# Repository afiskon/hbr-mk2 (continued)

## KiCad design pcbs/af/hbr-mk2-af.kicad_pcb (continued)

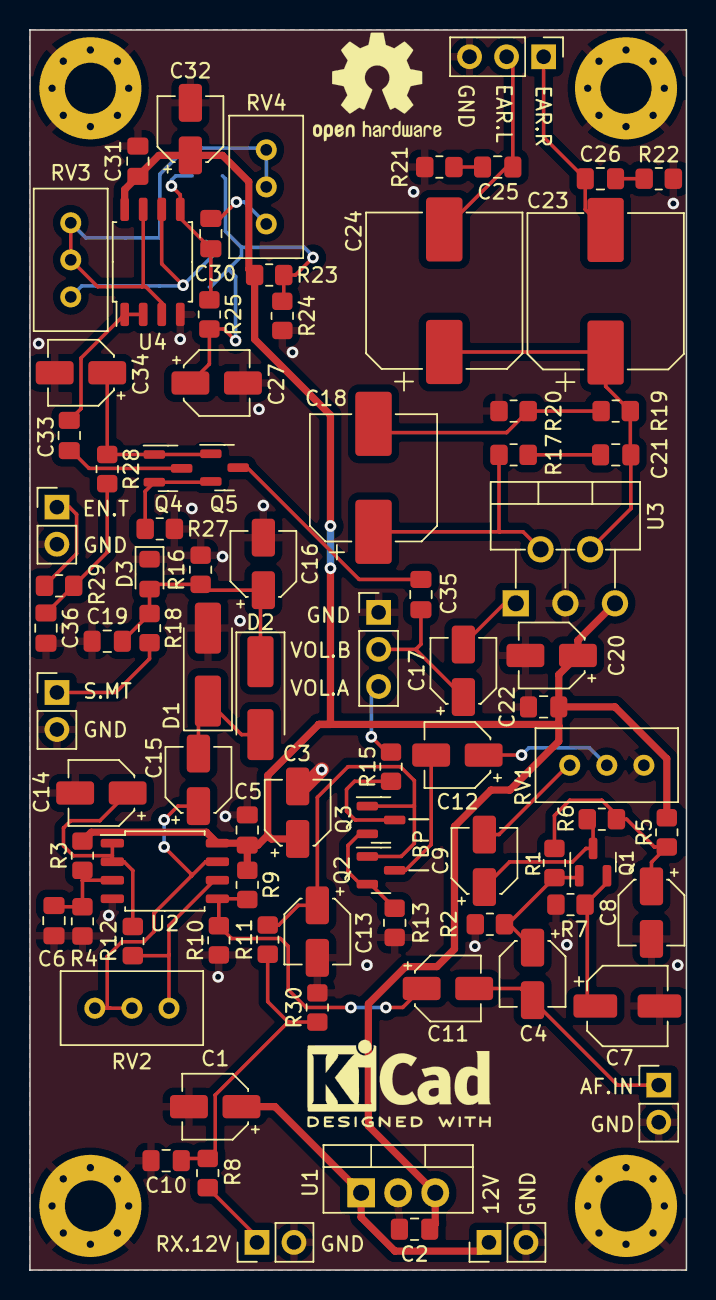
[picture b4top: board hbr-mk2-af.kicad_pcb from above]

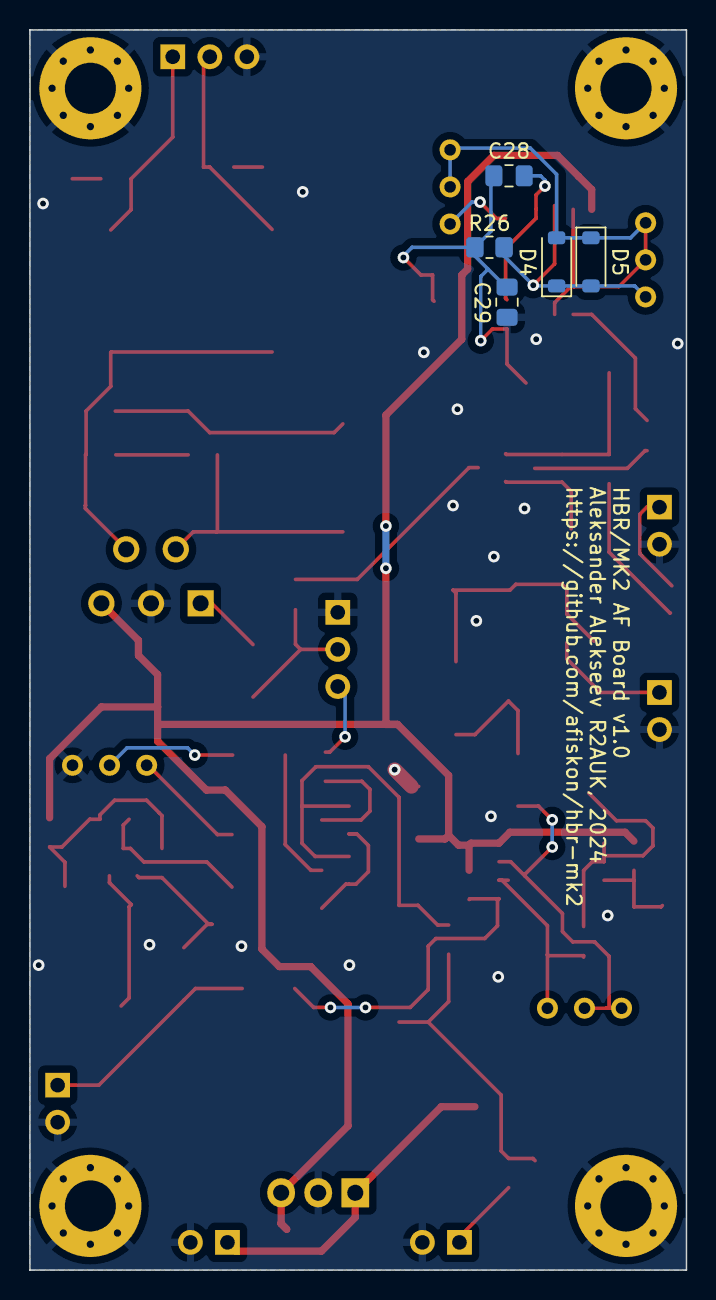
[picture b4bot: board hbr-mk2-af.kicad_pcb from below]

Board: 2 copper layers, 45.0 x 85.0 mm, 96 parts (5 on the bottom side), 47 nets.

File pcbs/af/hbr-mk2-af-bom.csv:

Reference(s),Qty,Value,Footprint
C1,1,1u,Capacitor_SMD:CP_Elec_4x5.4
"C2, C5, C6, C10, C19, C21, C22, C25, C26, C29, C31, C33, C36",13,0.1u,Capacitor_SMD:C_0805_2012Metric_Pad1.18x1.45mm_HandSolder
"C3, C4, C8, C9, C11, C12, C14, C15, C16, C20, C27, C32",12,10u,Capacitor_SMD:CP_Elec_4x5.4
C7,1,22u,Capacitor_SMD:CP_Elec_5x5.4
"C13, C34",2,4.7u,Capacitor_SMD:CP_Elec_4x5.4
C17,1,1u,Capacitor_SMD:CP_Elec_4x5.4
C18,1,220u,Capacitor_SMD:CP_Elec_8x10.5
"C23, C24",2,470u,Capacitor_SMD:CP_Elec_10x10.5
"C28, C30",2,4.7n,Capacitor_SMD:C_0805_2012Metric_Pad1.18x1.45mm_HandSolder
C35,1,100p,Capacitor_SMD:C_0805_2012Metric_Pad1.18x1.45mm_HandSolder
"D1, D2",2,SS14,Diode_SMD:D_SMA_Handsoldering
D3,1,Blue LED,LED_SMD:LED_0805_2012Metric_Pad1.15x1.40mm_HandSolder
"D4, D5",2,1N4148W,Diode_SMD:D_SOD-123
Q1,1,MMBT3904,Package_TO_SOT_SMD:SOT-23
"Q2, Q3, Q4, Q5",4,2N7002,Package_TO_SOT_SMD:SOT-23
"R1, R23, R24",3,100K,Resistor_SMD:R_0805_2012Metric_Pad1.20x1.40mm_HandSolder
"R2, R25",2,47K,Resistor_SMD:R_0805_2012Metric_Pad1.20x1.40mm_HandSolder
"R3, R4, R9, R10, R13, R16, R27, R30",8,10K,Resistor_SMD:R_0805_2012Metric_Pad1.20x1.40mm_HandSolder
R5,1,100,Resistor_SMD:R_0805_2012Metric_Pad1.20x1.40mm_HandSolder
"R6, R11, R28",3,2.2K,Resistor_SMD:R_0805_2012Metric_Pad1.20x1.40mm_HandSolder
"R7, R12",2,1K,Resistor_SMD:R_0805_2012Metric_Pad1.20x1.40mm_HandSolder
"R8, R18, R29",3,22,Resistor_SMD:R_0805_2012Metric_Pad1.20x1.40mm_HandSolder
R15,1,1.3K,Resistor_SMD:R_0805_2012Metric_Pad1.20x1.40mm_HandSolder
R17,1,220,Resistor_SMD:R_0805_2012Metric_Pad1.20x1.40mm_HandSolder
R19,1,680,Resistor_SMD:R_0805_2012Metric_Pad1.20x1.40mm_HandSolder
"R20, R21, R22",3,10,Resistor_SMD:R_0805_2012Metric_Pad1.20x1.40mm_HandSolder
R26,1,3.3K,Resistor_SMD:R_0805_2012Metric_Pad1.20x1.40mm_HandSolder
"RV1, RV3",2,10K,Potentiometer_THT:Potentiometer_Bourns_3296W_Vertical
RV2,1,500K,Potentiometer_THT:Potentiometer_Bourns_3296W_Vertical
RV4,1,100K,Potentiometer_THT:Potentiometer_Bourns_3296W_Vertical
U1,1,LM7808,Package_TO_SOT_THT:TO-220-3_Vertical
"U2, U4",2,NE5532,Package_SO:SOIC-8_5.23x5.23mm_P1.27mm
U3,1,TDA2003,Package_TO_SOT_THT:TO-220-5_P3.4x3.7mm_StaggerOdd_Lead3.8mm_Vertical

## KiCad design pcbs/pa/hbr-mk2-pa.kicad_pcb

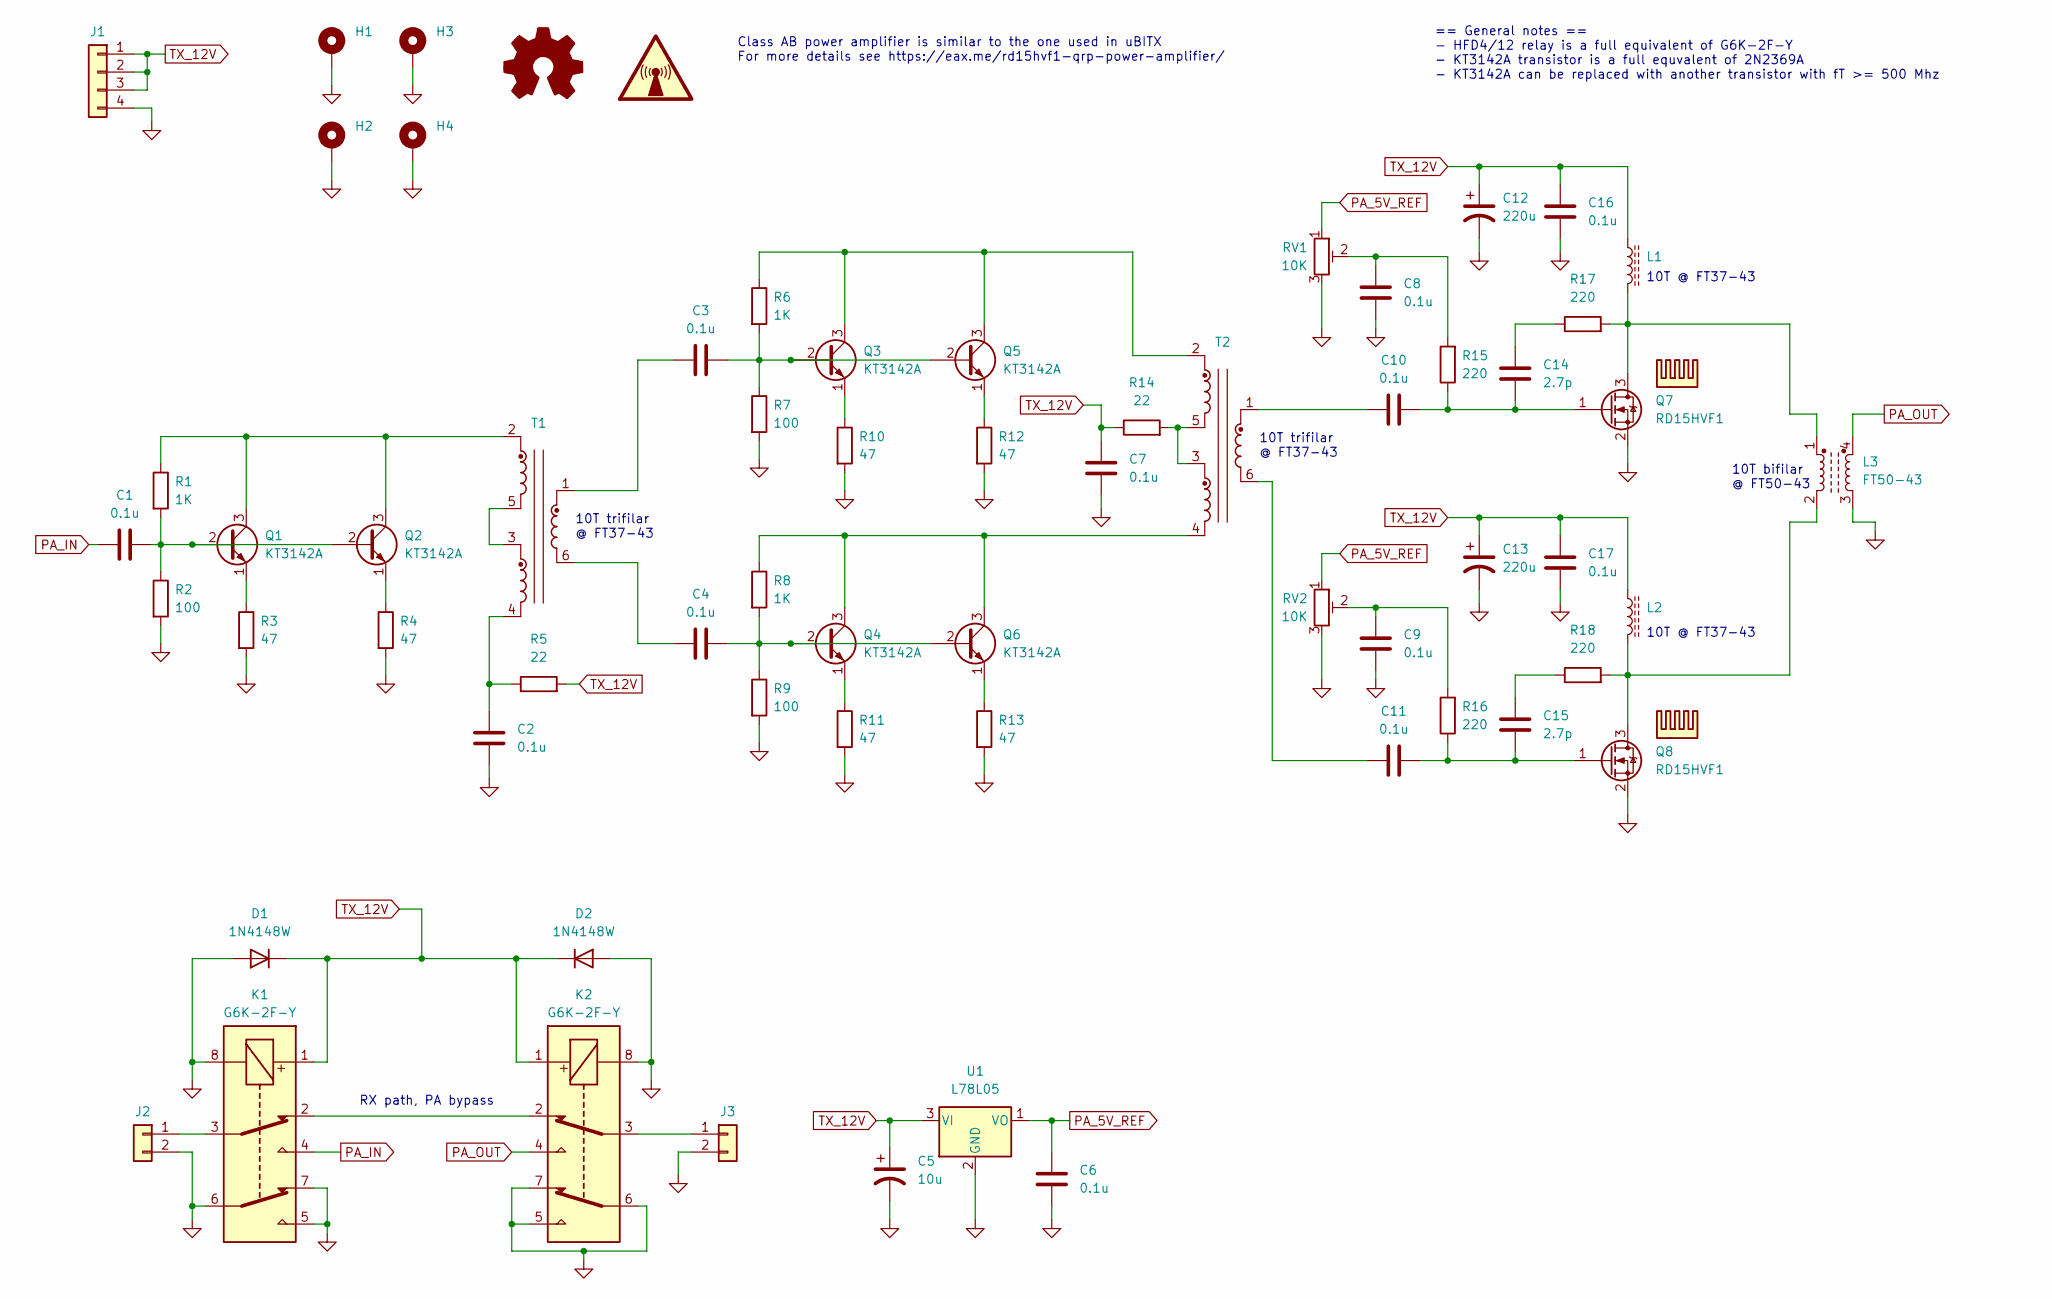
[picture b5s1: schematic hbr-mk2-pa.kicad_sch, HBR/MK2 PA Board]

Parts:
C1, C2, C3, C4, C6, C7, C8, C9, C10, C11, C16, C17: 0.1u; C_0805_2012Metric_Pad1.18x1.45mm_HandSolder
C5: 10u; CP_Elec_4x5.4
C12, C13: 220u; CP_Elec_8x10.5
C14, C15: 2.7p; C_0805_2012Metric_Pad1.18x1.45mm_HandSolder
D1, D2: 1N4148W; D_SOD-123
H1, H2, H3, H4: MountingHole_Pad; MountingHole_3.5mm_Pad_Via
HS1, HS2: Heatsink
J1: Conn_01x04; PinHeader_1x04_P2.54mm_Vertical
J2, J3: Conn_01x02; PinHeader_1x02_P2.54mm_Vertical
K1, K2: G6K-2F-Y; Relay_DPDT_Omron_G6K-2F-Y
L1, L2: FT37-43; L_Toroid_Vertical_L10.0mm_W5.0mm_P5.08mm
L3: FT50-43; DIP-4_W10.16mm
Q1, Q2, Q3, Q4, Q5, Q6: KT3142A; TO-18-3
Q7, Q8: RD15HVF1; TO-220-3_Horizontal_TabDown
R1, R6, R8: 1K; R_0805_2012Metric_Pad1.20x1.40mm_HandSolder
R2, R7, R9: 100; R_0805_2012Metric_Pad1.20x1.40mm_HandSolder
R3, R4, R10, R11, R12, R13: 47; R_0805_2012Metric_Pad1.20x1.40mm_HandSolder
R5, R14: 22; R_0805_2012Metric_Pad1.20x1.40mm_HandSolder
R15, R16, R17, R18: 220; R_0805_2012Metric_Pad1.20x1.40mm_HandSolder
RV1, RV2: 10K; Potentiometer_Bourns_3296W_Vertical
SYM1: Logo_Open_Hardware_Small; OSHW-Logo2_9.8x8mm_SilkScreen
SYM2: SYM_Radio_Waves_Large; KiCad-Logo2_5mm_SilkScreen
T1, T2: FT37-43; DIP-6_W7.62mm
U1: L78L05; TO-92_HandSolder

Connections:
GND: C2.2, C5.2, C6.2, C7.2, C8.2, C9.2, C12.2, C13.2, C16.2, C17.2, D1.2 (A), D2.2 (A), H1.1, H2.1, H3.1, H4.1, J1.4, J2.2, J3.2, K1.5, K1.6, K1.7, K1.8, K2.5, K2.6, K2.7, K2.8, L3.3, Q7.2 (S), Q8.2 (S), R2.2, R3.2, R4.2, R7.2, R9.2, R10.2, R11.2, R12.2, R13.2, RV1.3, RV2.3, U1.2 (GND)
unnamed: C2.1, R5.1, T1.4
unnamed: C3.1, T1.1
unnamed: C4.1, T1.6
unnamed: C8.1, R15.2, RV1.2
unnamed: C9.1, R16.2, RV2.2
unnamed: C10.1, T2.1
unnamed: C11.1, T2.6
unnamed: C14.1, R17.1
unnamed: C15.1, R18.1
unnamed: J2.1, K1.3
unnamed: J3.1, K2.3
unnamed: K1.2, K2.2
unnamed: C1.2, Q1.2 (B), Q2.2 (B), R1.2, R2.1
unnamed: Q1.3 (C), Q2.3 (C), R1.1, T1.2
unnamed: Q1.1 (E), R3.1
unnamed: Q2.1 (E), R4.1
unnamed: C3.2, Q3.2 (B), Q5.2 (B), R6.2, R7.1
unnamed: Q3.3 (C), Q5.3 (C), R6.1, T2.2
unnamed: Q3.1 (E), R10.1
unnamed: C4.2, Q4.2 (B), Q6.2 (B), R8.2, R9.1
unnamed: Q4.3 (C), Q6.3 (C), R8.1, T2.4
unnamed: Q4.1 (E), R11.1
unnamed: Q5.1 (E), R12.1
unnamed: Q6.1 (E), R13.1
unnamed: L1.2, L3.1, Q7.3 (D), R17.2
unnamed: C10.2, C14.2, Q7.1 (G), R15.1
unnamed: L2.2, L3.2, Q8.3 (D), R18.2
unnamed: C11.2, C15.2, Q8.1 (G), R16.1
unnamed: R14.2, T2.3, T2.5
unnamed: T1.3, T1.5
PA_5V_REF: C6.1, RV1.1, RV2.1, U1.1 (VO)
PA_IN: C1.1, K1.4
PA_OUT: K2.4, L3.4
TX_12V: C5.1, C7.1, C12.1, C13.1, C16.1, C17.1, D1.1 (K), D2.1 (K), J1.1, J1.2, J1.3, K1.1, K2.1, L1.1, L2.1, R5.2, R14.1, U1.3 (VI)

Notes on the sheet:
10T trifilar @ FT37-43
== General notes == - HFD4/12 relay is a full equivalent of G6K-2F-Y - KT3142A transistor is a full equvalent of 2N2369A - KT3142A can be replaced with another transistor with fT >= 500 Mhz
10T bifilar @ FT50-43
10T @ FT37-43
RX path, PA bypass
Class AB power amplifier is similar to the one used in uBITX For more details see https://eax.me/rd15hvf1-qrp-power-amplifier/

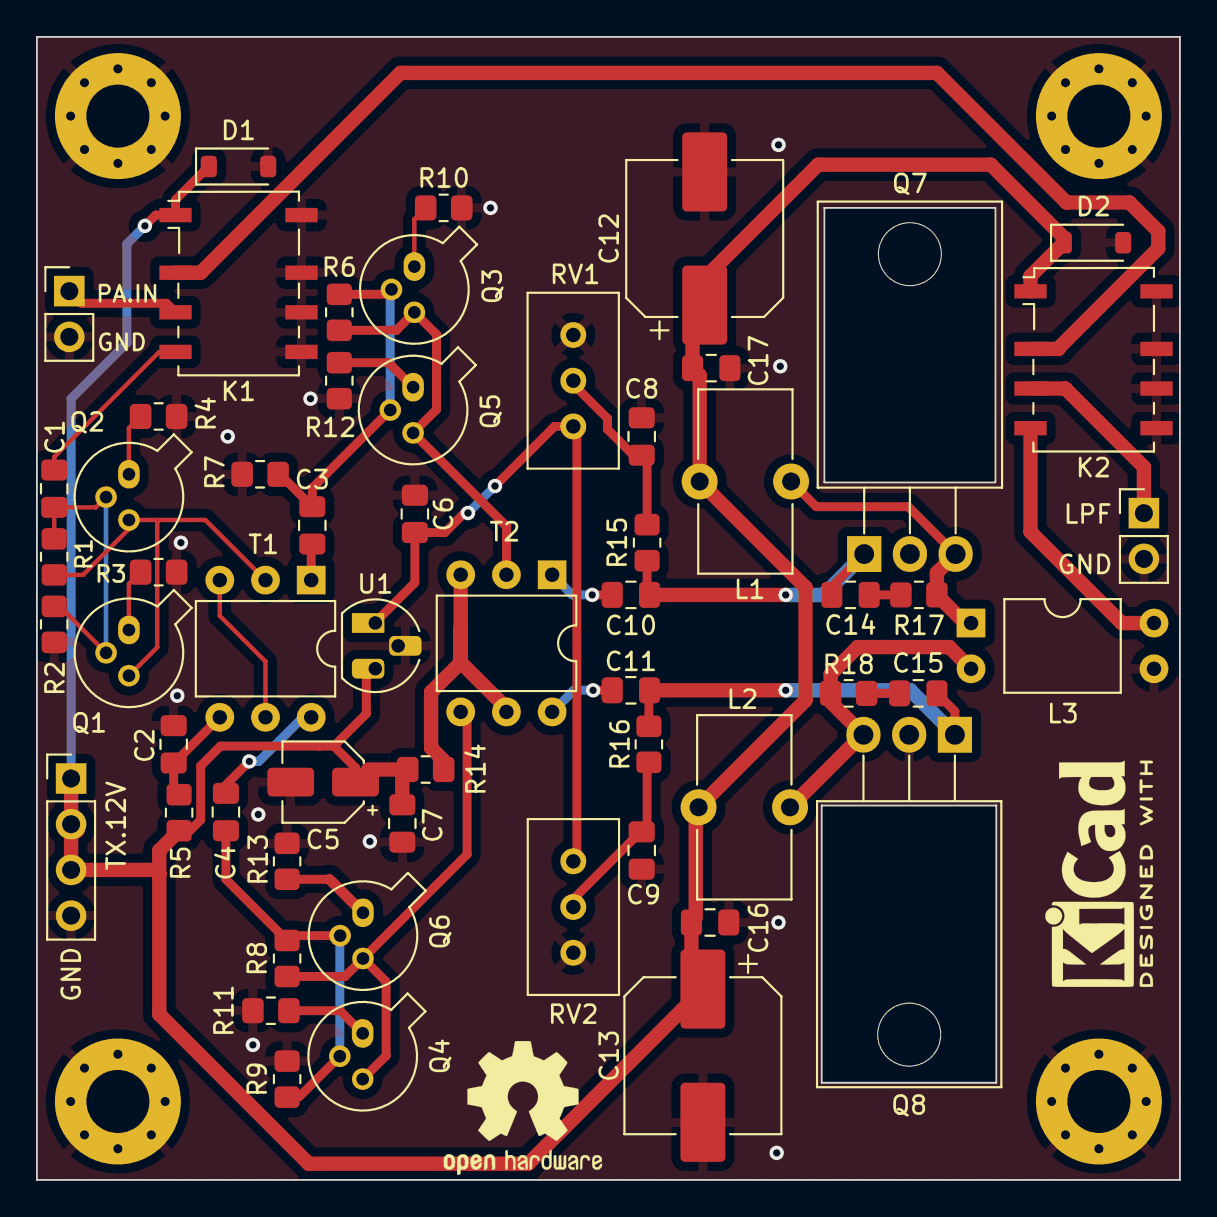
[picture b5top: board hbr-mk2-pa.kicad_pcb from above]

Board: 2 copper layers, 63.5 x 63.5 mm, 64 parts (0 on the bottom side), 35 nets.

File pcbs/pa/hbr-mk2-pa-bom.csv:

Reference(s),Qty,Value,Footprint
"C1, C2, C3, C4, C6, C7, C8, C9, C10, C11, C16, C17",12,0.1u,Capacitor_SMD:C_0805_2012Metric_Pad1.18x1.45mm_HandSolder
C5,1,10u,Capacitor_SMD:CP_Elec_4x5.4
"C12, C13",2,220u,Capacitor_SMD:CP_Elec_8x10.5
"C14, C15",2,2.7p,Capacitor_SMD:C_0805_2012Metric_Pad1.18x1.45mm_HandSolder
"D1, D2",2,1N4148W,Diode_SMD:D_SOD-123
"K1, K2",2,G6K-2F-Y,Relay_SMD:Relay_DPDT_Omron_G6K-2F-Y
"L1, L2",2,FT37-43,Inductor_THT:L_Toroid_Vertical_L10.0mm_W5.0mm_P5.08mm
L3,1,FT50-43,Package_DIP:DIP-4_W10.16mm
"Q1, Q2, Q3, Q4, Q5, Q6",6,KT3142A,Package_TO_SOT_THT:TO-18-3
"Q7, Q8",2,RD15HVF1,Package_TO_SOT_THT:TO-220-3_Horizontal_TabDown
"R1, R6, R8",3,1K,Resistor_SMD:R_0805_2012Metric_Pad1.20x1.40mm_HandSolder
"R2, R7, R9",3,100,Resistor_SMD:R_0805_2012Metric_Pad1.20x1.40mm_HandSolder
"R3, R4, R10, R11, R12, R13",6,47,Resistor_SMD:R_0805_2012Metric_Pad1.20x1.40mm_HandSolder
"R5, R14",2,22,Resistor_SMD:R_0805_2012Metric_Pad1.20x1.40mm_HandSolder
"R15, R16, R17, R18",4,220,Resistor_SMD:R_0805_2012Metric_Pad1.20x1.40mm_HandSolder
"RV1, RV2",2,10K,Potentiometer_THT:Potentiometer_Bourns_3296W_Vertical
"T1, T2",2,FT37-43,Package_DIP:DIP-6_W7.62mm
U1,1,L78L05,Package_TO_SOT_THT:TO-92_HandSolder

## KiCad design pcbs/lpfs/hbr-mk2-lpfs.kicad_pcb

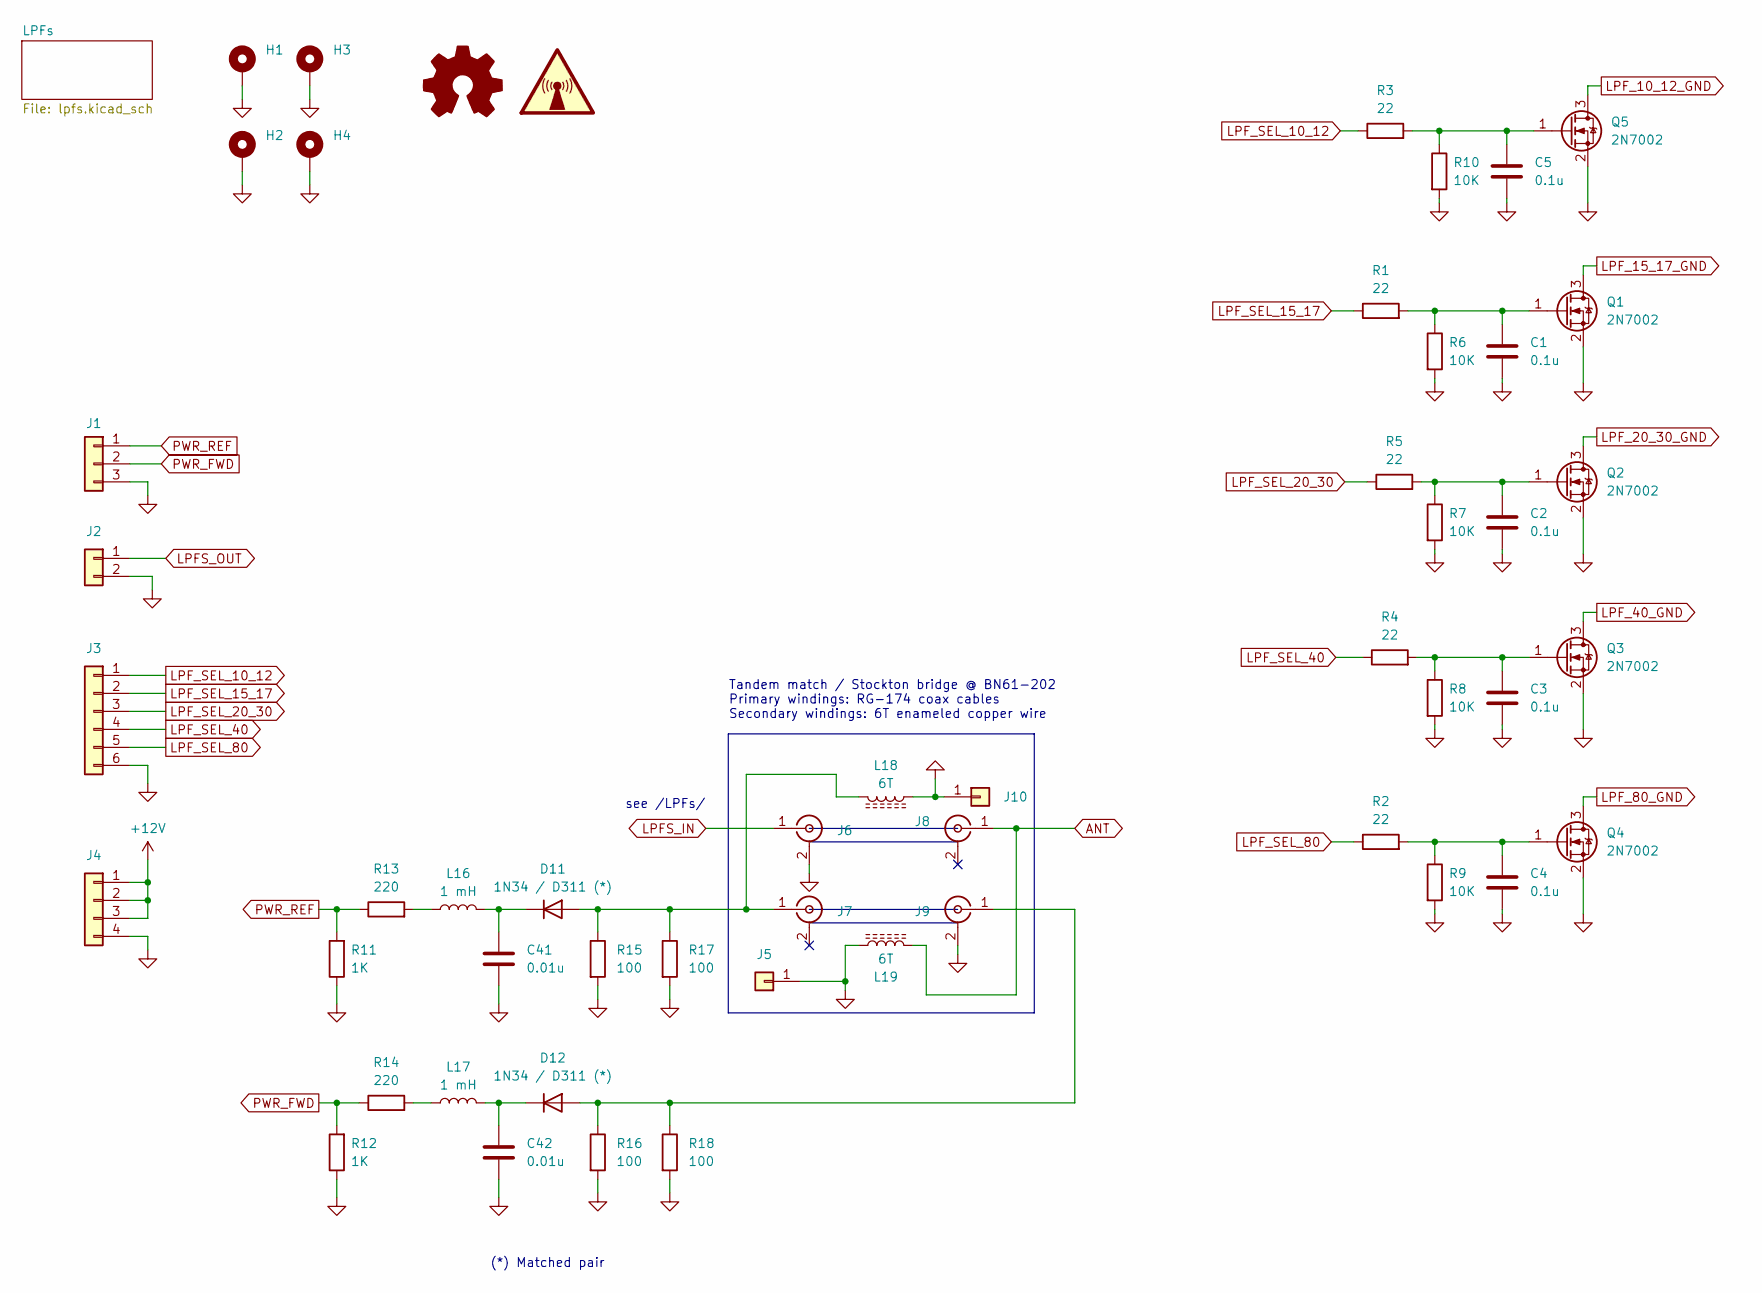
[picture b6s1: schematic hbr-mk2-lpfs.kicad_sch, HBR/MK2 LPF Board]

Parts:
C1, C2, C3, C4, C5: 0.1u; C_0805_2012Metric_Pad1.18x1.45mm_HandSolder
C41, C42: 0.01u; C_0805_2012Metric_Pad1.18x1.45mm_HandSolder
D11, D12: 1N34 / D311 (*); D_DO-34_SOD68_P2.54mm_Vertical_AnodeUp
H1, H2, H3, H4: MountingHole_Pad; MountingHole_3.5mm_Pad_Via
J1: Conn_01x03; PinSocket_1x03_P2.54mm_Vertical
J2: Conn_01x02; PinSocket_1x02_P2.54mm_Vertical
J3: Conn_01x06; PinSocket_1x06_P2.54mm_Vertical
J4: Conn_01x04; PinSocket_1x04_P2.54mm_Vertical
J5, J10: Conn_01x01; PinSocket_1x01_P2.54mm_Vertical
J6, J7, J8, J9: Conn_Coaxial; PinSocket_1x02_P2.54mm_Vertical
L16, L17: 1 mH; L_Axial_L7.0mm_D3.3mm_P2.54mm_Vertical_Fastron_MICC
L18, L19: 6T
Q1, Q2, Q3, Q4, Q5: 2N7002; SOT-23
R1, R2, R3, R4, R5: 22; R_0805_2012Metric_Pad1.20x1.40mm_HandSolder
R6, R7, R8, R9, R10: 10K; R_0805_2012Metric_Pad1.20x1.40mm_HandSolder
R11, R12: 1K; R_0805_2012Metric_Pad1.20x1.40mm_HandSolder
R13, R14: 220; R_0805_2012Metric_Pad1.20x1.40mm_HandSolder
R15, R16, R17, R18: 100; R_0805_2012Metric_Pad1.20x1.40mm_HandSolder
SYM1: Logo_Open_Hardware_Small; OSHW-Logo2_9.8x8mm_SilkScreen
SYM2: SYM_Radio_Waves_Large; KiCad-Logo2_5mm_SilkScreen

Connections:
+12V: J4.1, J4.2, J4.3; also elsewhere on the board
ANT: J8.1 (In), L19.1
GND: C1.2, C2.2, C3.2, C4.2, C5.2, C41.2, C42.2, H1.1, H2.1, H3.1, H4.1, J1.3, J2.2, J3.6, J4.4, J5.1, J6.2 (Ext), J9.2 (Ext), J10.1, L18.1, L19.2, Q1.2 (S), Q2.2 (S), Q3.2 (S), Q4.2 (S), Q5.2 (S), R6.2, R7.2, R8.2, R9.2, R10.2, R11.1, R12.1, R15.2, R16.2, R17.2, R18.2; also elsewhere on the board
LPFS_IN: J6.1 (In); also elsewhere on the board
LPFS_OUT: J2.1; also elsewhere on the board
LPF_10_12_GND: Q5.3 (D); also elsewhere on the board
LPF_15_17_GND: Q1.3 (D); also elsewhere on the board
LPF_20_30_GND: Q2.3 (D); also elsewhere on the board
LPF_40_GND: Q3.3 (D); also elsewhere on the board
LPF_80_GND: Q4.3 (D); also elsewhere on the board
LPF_SEL_10_12: J3.1, R3.1
LPF_SEL_15_17: J3.2, R1.1
LPF_SEL_20_30: J3.3, R5.1
LPF_SEL_40: J3.4, R4.1
LPF_SEL_80: J3.5, R2.1
unnamed: D11.2 (A), J7.1 (In), L18.2, R15.1, R17.1
unnamed: C41.1, D11.1 (K), L16.2
unnamed: D12.2 (A), J9.1 (In), R16.1, R18.1
unnamed: C42.1, D12.1 (K), L17.2
unnamed: L16.1, R13.2
unnamed: L17.1, R14.2
unnamed: C1.1, Q1.1 (G), R1.2, R6.1
unnamed: C2.1, Q2.1 (G), R5.2, R7.1
unnamed: C3.1, Q3.1 (G), R4.2, R8.1
unnamed: C4.1, Q4.1 (G), R2.2, R9.1
unnamed: C5.1, Q5.1 (G), R3.2, R10.1
PWR_FWD: J1.2, R12.2, R14.1
PWR_REF: J1.1, R11.2, R13.1

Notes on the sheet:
see /LPFs/
Tandem match / Stockton bridge @ BN61-202 Primary windings: RG-174 coax cables Secondary windings: 6T enameled copper wire
(*) Matched pair

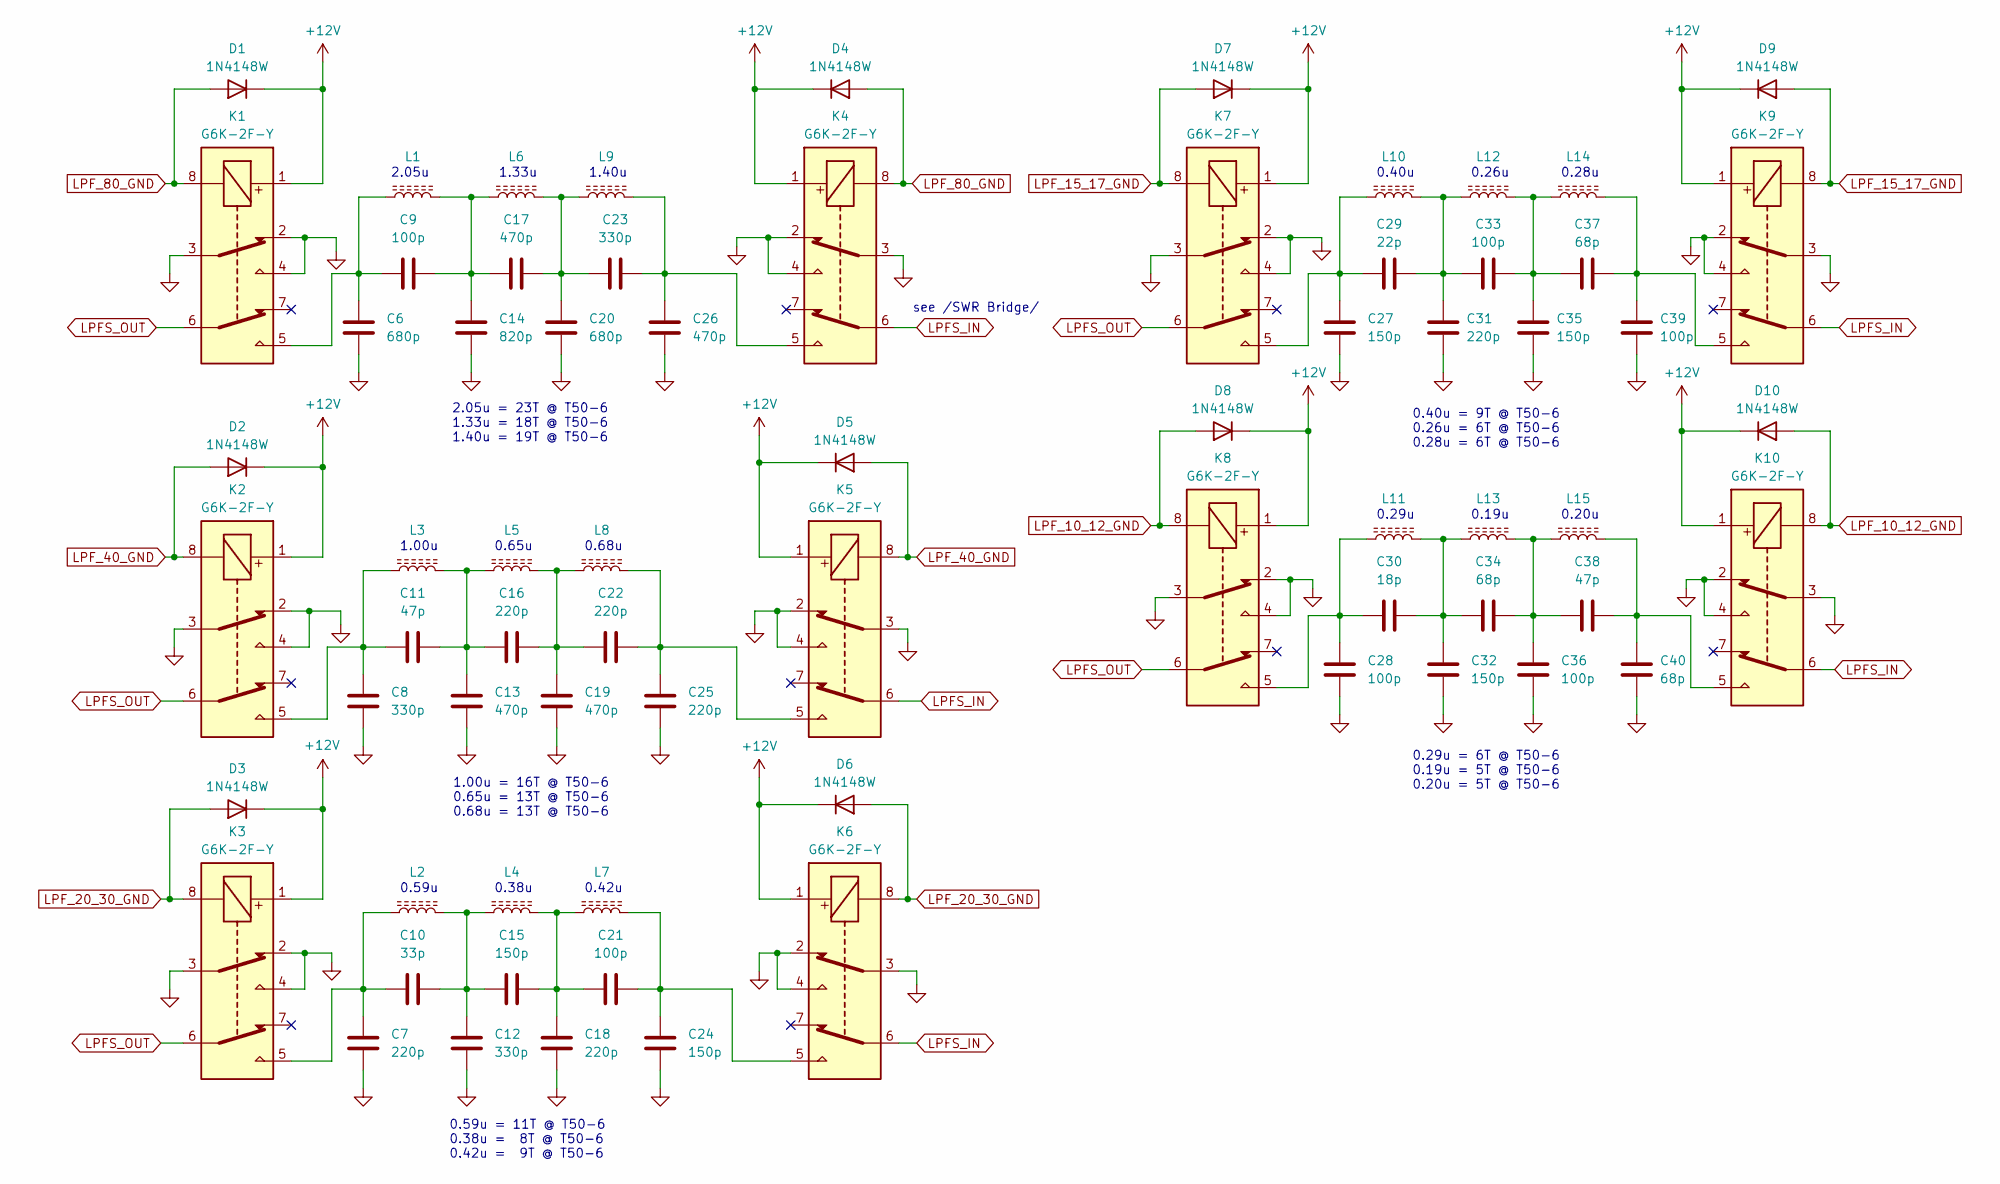
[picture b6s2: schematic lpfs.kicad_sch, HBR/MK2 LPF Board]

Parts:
C6, C20: 680p; C_0805_2012Metric_Pad1.18x1.45mm_HandSolder
C7, C16, C18, C22, C25, C31: 220p; C_0805_2012Metric_Pad1.18x1.45mm_HandSolder
C8, C12, C23: 330p; C_0805_2012Metric_Pad1.18x1.45mm_HandSolder
C9, C21, C28, C33, C36, C39: 100p; C_0805_2012Metric_Pad1.18x1.45mm_HandSolder
C10: 33p; C_0805_2012Metric_Pad1.18x1.45mm_HandSolder
C11, C38: 47p; C_0805_2012Metric_Pad1.18x1.45mm_HandSolder
C13, C17, C19, C26: 470p; C_0805_2012Metric_Pad1.18x1.45mm_HandSolder
C14: 820p; C_0805_2012Metric_Pad1.18x1.45mm_HandSolder
C15, C24, C27, C32, C35: 150p; C_0805_2012Metric_Pad1.18x1.45mm_HandSolder
C29: 22p; C_0805_2012Metric_Pad1.18x1.45mm_HandSolder
C30: 18p; C_0805_2012Metric_Pad1.18x1.45mm_HandSolder
C34, C37, C40: 68p; C_0805_2012Metric_Pad1.18x1.45mm_HandSolder
D1, D2, D3, D4, D5, D6, D7, D8, D9, D10: 1N4148W; D_SOD-123
K1, K2, K3, K4, K5, K6, K7, K8, K9, K10: G6K-2F-Y; Relay_DPDT_Omron_G6K-2F-Y
L1, L2, L3, L4, L5, L6, L7, L8, L9, L10, L11, L12, L13, L14, L15: T50-6; L_Toroid_Vertical_L13.0mm_W6.5mm_P5.60mm

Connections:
+12V: D1.1 (K), D2.1 (K), D3.1 (K), D4.1 (K), D5.1 (K), D6.1 (K), D7.1 (K), D8.1 (K), D9.1 (K), D10.1 (K), K1.1, K2.1, K3.1, K4.1, K5.1, K6.1, K7.1, K8.1, K9.1, K10.1; also elsewhere on the board
GND: C6.2, C7.2, C8.2, C12.2, C13.2, C14.2, C18.2, C19.2, C20.2, C24.2, C25.2, C26.2, C27.2, C28.2, C31.2, C32.2, C35.2, C36.2, C39.2, C40.2, K1.2, K1.3, K1.4, K2.2, K2.3, K2.4, K3.2, K3.3, K3.4, K4.2, K4.3, K4.4, K5.2, K5.3, K5.4, K6.2, K6.3, K6.4, K7.2, K7.3, K7.4, K8.2, K8.3, K8.4, K9.2, K9.3, K9.4, K10.2, K10.3, K10.4; also elsewhere on the board
LPFS_IN: K4.6, K5.6, K6.6, K9.6, K10.6; also elsewhere on the board
LPFS_OUT: K1.6, K2.6, K3.6, K7.6, K8.6; also elsewhere on the board
LPF_10_12_GND: D8.2 (A), D10.2 (A), K8.8, K10.8; also elsewhere on the board
LPF_15_17_GND: D7.2 (A), D9.2 (A), K7.8, K9.8; also elsewhere on the board
LPF_20_30_GND: D3.2 (A), D6.2 (A), K3.8, K6.8; also elsewhere on the board
LPF_40_GND: D2.2 (A), D5.2 (A), K2.8, K5.8; also elsewhere on the board
LPF_80_GND: D1.2 (A), D4.2 (A), K1.8, K4.8; also elsewhere on the board
unnamed: C6.1, C9.1, K1.5, L1.1
unnamed: C7.1, C10.1, K3.5, L2.1
unnamed: C10.2, C12.1, C15.1, L2.2, L4.1
unnamed: C8.1, C11.1, K2.5, L3.1
unnamed: C11.2, C13.1, C16.1, L3.2, L5.1
unnamed: C9.2, C14.1, C17.1, L1.2, L6.1
unnamed: C15.2, C18.1, C21.1, L4.2, L7.1
unnamed: C16.2, C19.1, C22.1, L5.2, L8.1
unnamed: C17.2, C20.1, C23.1, L6.2, L9.1
unnamed: C21.2, C24.1, K6.5, L7.2
unnamed: C22.2, C25.1, K5.5, L8.2
unnamed: C23.2, C26.1, K4.5, L9.2
unnamed: C27.1, C29.1, K7.5, L10.1
unnamed: C28.1, C30.1, K8.5, L11.1
unnamed: C29.2, C31.1, C33.1, L10.2, L12.1
unnamed: C30.2, C32.1, C34.1, L11.2, L13.1
unnamed: C33.2, C35.1, C37.1, L12.2, L14.1
unnamed: C34.2, C36.1, C38.1, L13.2, L15.1
unnamed: C37.2, C39.1, K9.5, L14.2
unnamed: C38.2, C40.1, K10.5, L15.2

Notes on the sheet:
0.68u
0.40u
0.59u
1.00u
0.19u
0.28u
0.40u = 9T @ T50-6 0.26u = 6T @ T50-6 0.28u = 6T @ T50-6
0.38u
0.42u
2.05u = 23T @ T50-6 1.33u = 18T @ T50-6 1.40u = 19T @ T50-6
see /SWR Bridge/
0.59u = 11T @ T50-6 0.38u = 8T @ T50-6 0.42u = 9T @ T50-6
2.05u
1.00u = 16T @ T50-6 0.65u = 13T @ T50-6 0.68u = 13T @ T50-6
1.40u
0.65u
0.29u
1.33u
0.26u
0.29u = 6T @ T50-6 0.19u = 5T @ T50-6 0.20u = 5T @ T50-6
0.20u

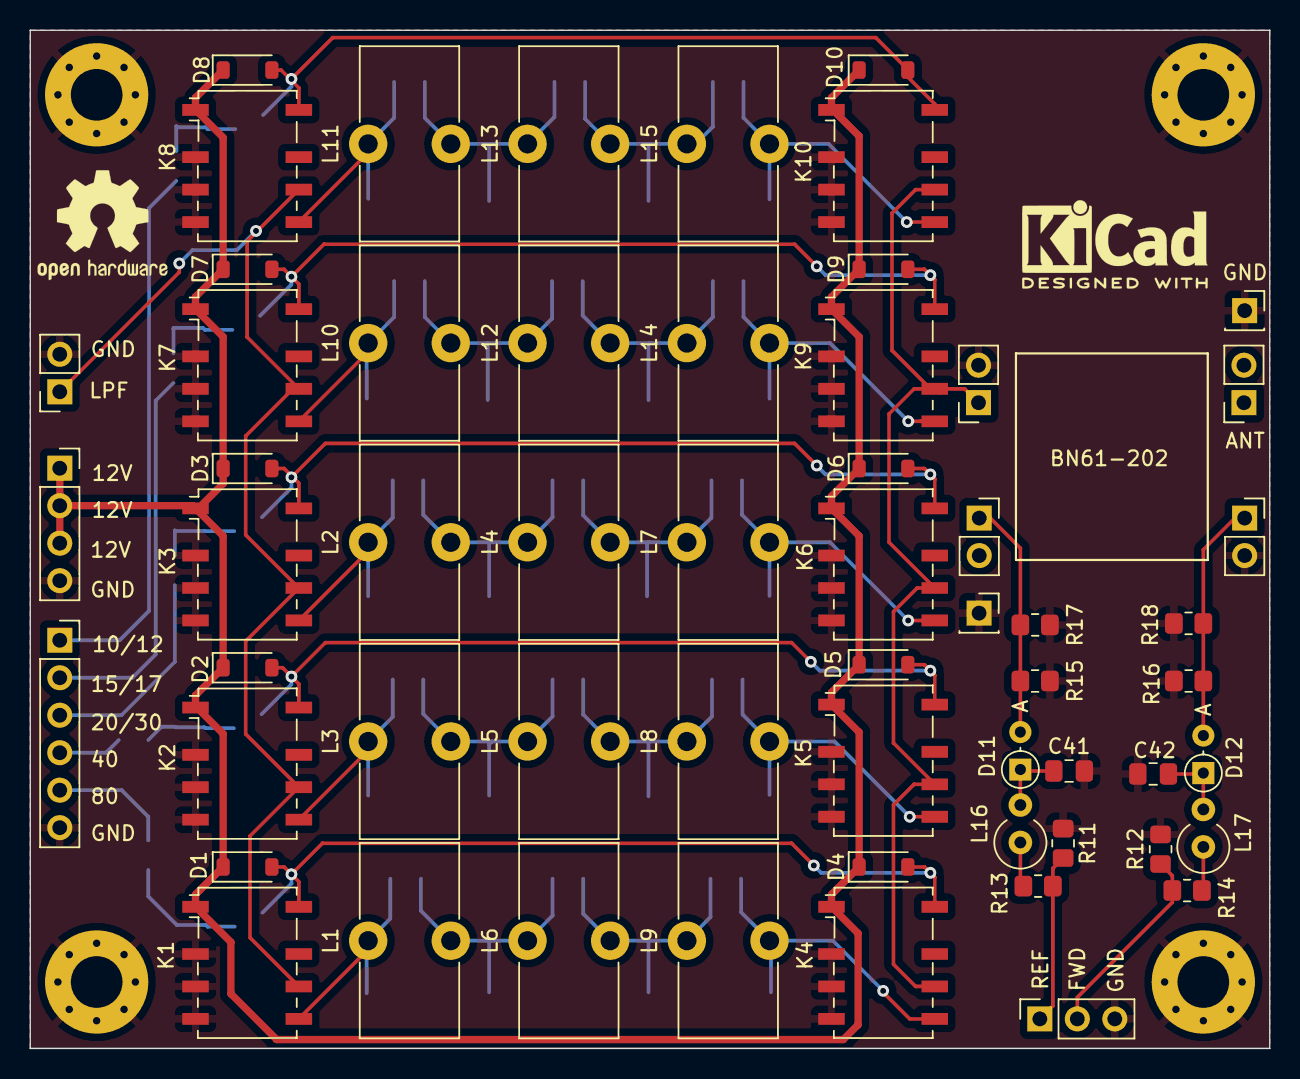
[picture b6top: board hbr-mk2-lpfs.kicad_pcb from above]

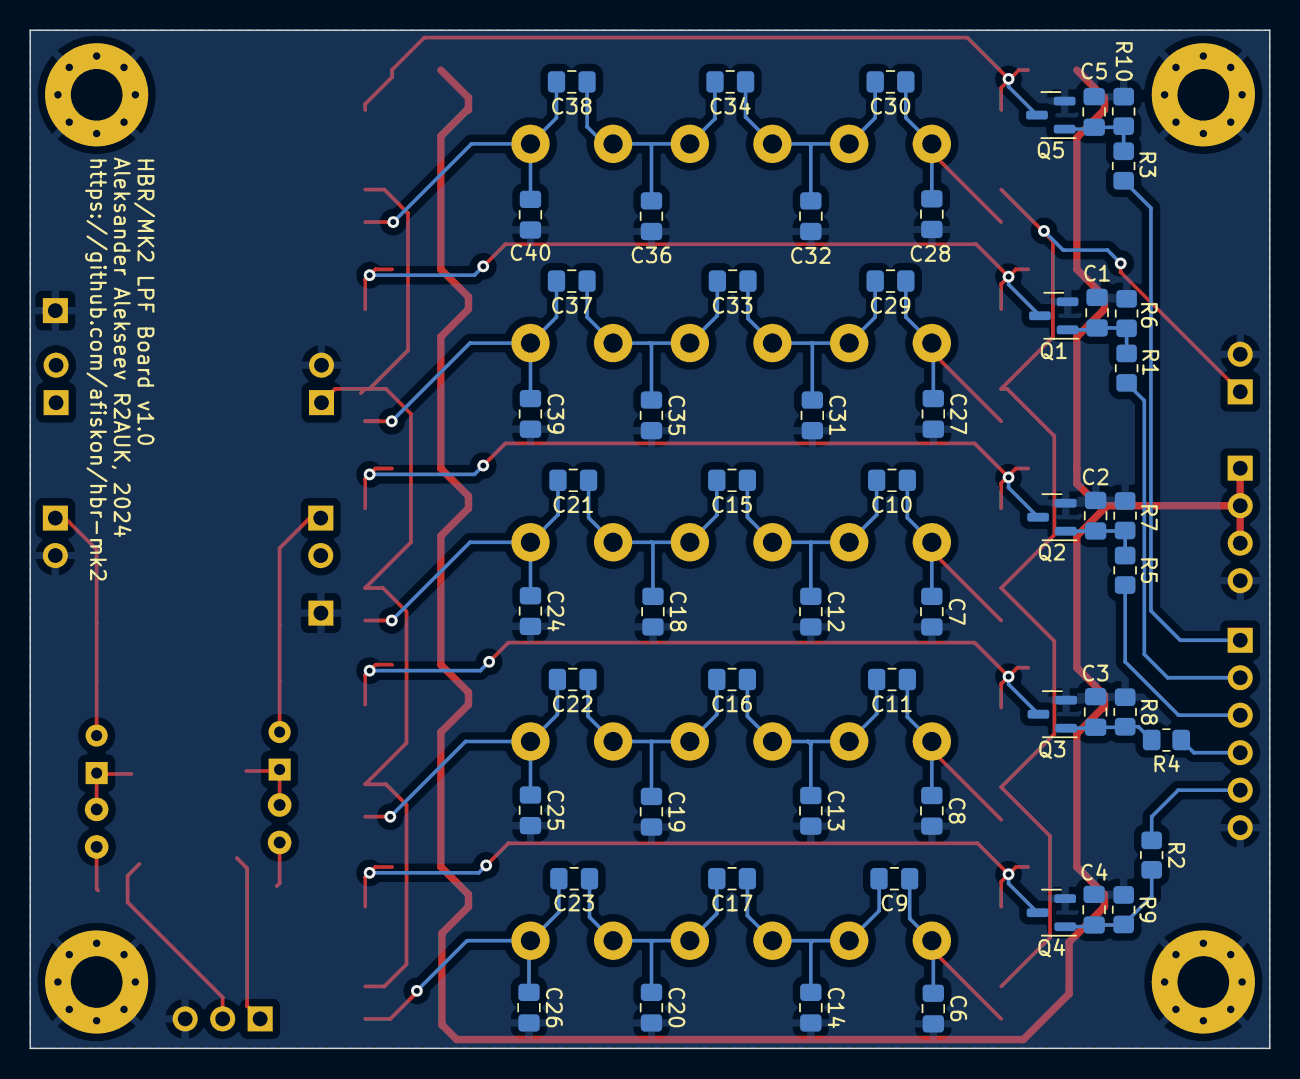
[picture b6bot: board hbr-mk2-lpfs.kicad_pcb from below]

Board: 2 copper layers, 84.0 x 69.0 mm, 120 parts (55 on the bottom side), 47 nets.

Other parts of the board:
J11: Conn_01x01; PinSocket_1x01_P2.54mm_Vertical

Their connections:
GND: J11.1; also elsewhere on the board

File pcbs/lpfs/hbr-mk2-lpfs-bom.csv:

Reference(s),Qty,Value,Footprint
"C1, C2, C3, C4, C5",5,0.1u,Capacitor_SMD:C_0805_2012Metric_Pad1.18x1.45mm_HandSolder
"C6, C20",2,680p,Capacitor_SMD:C_0805_2012Metric_Pad1.18x1.45mm_HandSolder
"C7, C16, C18, C22, C25, C31",6,220p,Capacitor_SMD:C_0805_2012Metric_Pad1.18x1.45mm_HandSolder
"C8, C12, C23",3,330p,Capacitor_SMD:C_0805_2012Metric_Pad1.18x1.45mm_HandSolder
"C9, C21, C28, C33, C36, C39",6,100p,Capacitor_SMD:C_0805_2012Metric_Pad1.18x1.45mm_HandSolder
C10,1,33p,Capacitor_SMD:C_0805_2012Metric_Pad1.18x1.45mm_HandSolder
"C11, C38",2,47p,Capacitor_SMD:C_0805_2012Metric_Pad1.18x1.45mm_HandSolder
"C13, C17, C19, C26",4,470p,Capacitor_SMD:C_0805_2012Metric_Pad1.18x1.45mm_HandSolder
C14,1,820p,Capacitor_SMD:C_0805_2012Metric_Pad1.18x1.45mm_HandSolder
"C15, C24, C27, C32, C35",5,150p,Capacitor_SMD:C_0805_2012Metric_Pad1.18x1.45mm_HandSolder
C29,1,22p,Capacitor_SMD:C_0805_2012Metric_Pad1.18x1.45mm_HandSolder
C30,1,18p,Capacitor_SMD:C_0805_2012Metric_Pad1.18x1.45mm_HandSolder
"C34, C37, C40",3,68p,Capacitor_SMD:C_0805_2012Metric_Pad1.18x1.45mm_HandSolder
"C41, C42",2,0.01u,Capacitor_SMD:C_0805_2012Metric_Pad1.18x1.45mm_HandSolder
"D1, D2, D3, D4, D5, D6, D7, D8, D9, D10",10,1N4148W,Diode_SMD:D_SOD-123
"D11, D12",2 (matched),1N34/D311,Diode_THT:D_DO-34_SOD68_P2.54mm_Vertical_AnodeUp
"K1, K2, K3, K4, K5, K6, K7, K8, K9, K10",10,G6K-2F-Y,Relay_SMD:Relay_DPDT_Omron_G6K-2F-Y
"L1, L2, L3, L4, L5, L6, L7, L8, L9, L10, L11, L12, L13, L14, L15",15,T50-6,Inductor_THT:L_Toroid_Vertical_L13.0mm_W6.5mm_P5.60mm
"L16, L17",2,1 mH,Inductor_THT:L_Axial_L7.0mm_D3.3mm_P2.54mm_Vertical_Fastron_MICC
"Q1, Q2, Q3, Q4, Q5",5,2N7002,Package_TO_SOT_SMD:SOT-23
"R1, R2, R3, R4, R5",5,22,Resistor_SMD:R_0805_2012Metric_Pad1.20x1.40mm_HandSolder
"R6, R7, R8, R9, R10",5,10K,Resistor_SMD:R_0805_2012Metric_Pad1.20x1.40mm_HandSolder
"R11, R12",2,1K,Resistor_SMD:R_0805_2012Metric_Pad1.20x1.40mm_HandSolder
"R13, R14",2,220,Resistor_SMD:R_0805_2012Metric_Pad1.20x1.40mm_HandSolder
"R15, R16, R17, R18",4,100,Resistor_SMD:R_0805_2012Metric_Pad1.20x1.40mm_HandSolder
"L18, L19",1,BN61-202,---
